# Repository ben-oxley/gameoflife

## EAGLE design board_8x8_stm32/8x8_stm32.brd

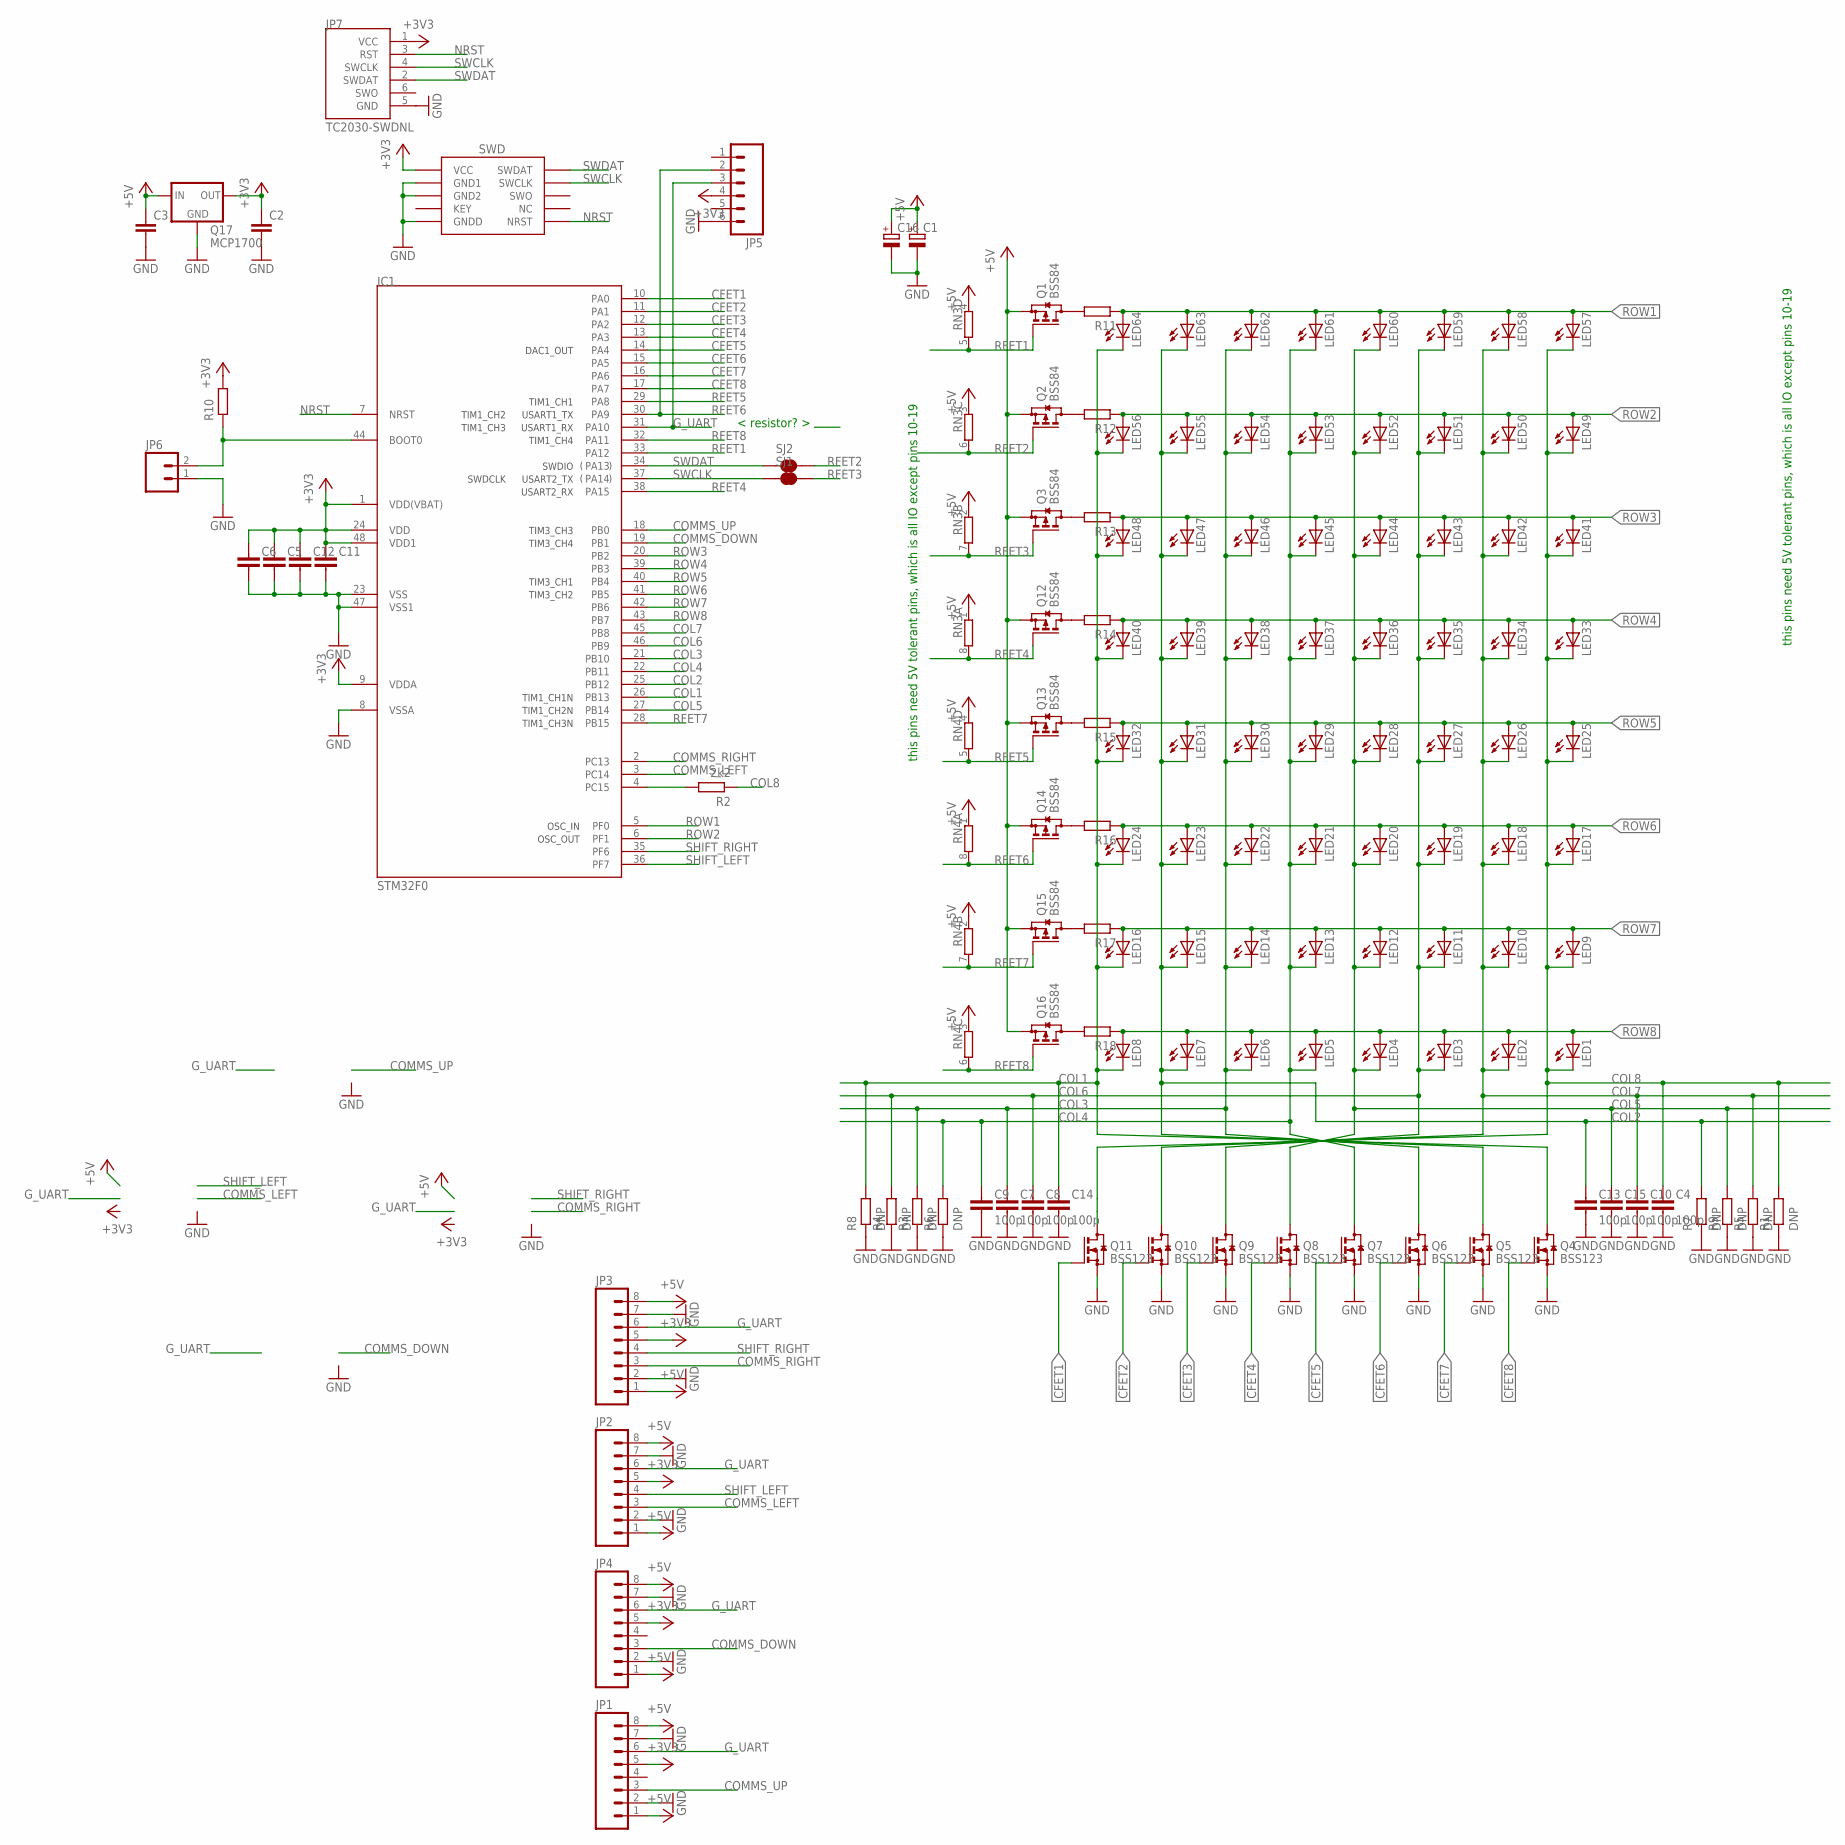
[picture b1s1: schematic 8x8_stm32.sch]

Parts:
C1, C16: CPOL-EUE2-4; E2-4
C2, C3: C-EU050-025X075; C050-025X075
C4, C7, C8, C9, C10, C13, C14, C15: 100p; C0603-N
C5, C6, C11, C12: CAPACITOR0603-N; C0603-N
IC1: STM32F0; TQFP48
J1: SWD_SHROUD; SWD_PTH_SHROUD
JP1, JP2, JP3, JP4: M08; 1X08_ROUND
JP5: M06SILK_FEMALE_PTH; 1X06
JP6: M02PTH; 1X02
JP7: TC2030-SWDNL; TC2030-MCP-NL
LED1, LED2, LED3, LED4, LED5, LED6, LED7, LED8, LED9, LED10, LED11, LED12, LED13, LED14, LED15, LED16, LED17, LED18, LED19, LED20, LED21, LED22, LED23, LED24, LED25, LED26, LED27, LED28, LED29, LED30, LED31, LED32, LED33, LED34, LED35, LED36, LED37, LED38, LED39, LED40, LED41, LED42, LED43, LED44, LED45, LED46, LED47, LED48, LED49, LED50, LED51, LED52, LED53, LED54, LED55, LED56, LED57, LED58, LED59, LED60, LED61, LED62, LED63, LED64: LED5MM/0603; LED5MM/SMD
Q1, Q2, Q3, Q12, Q13, Q14, Q15, Q16: BSS84; SOT23
Q4, Q5, Q6, Q7, Q8, Q9, Q10, Q11: BSS123; SOT23
Q17: MCP1700; TO92-INLINE
R1, R3, R4, R5, R6, R7, R8, R9: DNP; R0603-N
R2: 2k2; R0603-N
R10, R11, R12, R13, R14, R15, R16, R17, R18: RESISTOR0603-N; R0603-N
RN3, RN4: 4R-NEXB38V; EXB38V
SJ1, SJ2: JUMPER-PAD-2-NC_BY_TRACE; PAD-JUMPER-2-NC_BY_TRACE_YES_SILK

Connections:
+3V3: C2.1, C5.1, C6.1, C11.1, C12.1, IC1.1 (VDD(VBAT)), IC1.9 (VDDA), IC1.24 (VDD), IC1.48 (VDD1), J1.1 (VCC), JP1.5, JP2.5, JP3.5, JP4.5, JP5.4, JP7.1 (VCC), Q17.VOUT (OUT), R10.2
+5V: C1.+, C3.1, C16.+, JP1.1, JP1.8, JP2.1, JP2.8, JP3.1, JP3.8, JP4.1, JP4.8, Q1.2 (S), Q2.2 (S), Q3.2 (S), Q12.2 (S), Q13.2 (S), Q14.2 (S), Q15.2 (S), Q16.2 (S), Q17.VIN (IN), RN3.1, RN3.2 (1), RN3.3 (1), RN3.4 (1), RN4.1, RN4.2 (1), RN4.3 (1), RN4.4 (1)
CFET1: IC1.10 (PA0), Q11.1 (G)
CFET2: IC1.11 (PA1), Q10.1 (G)
CFET3: IC1.12 (PA2), Q9.1 (G)
CFET4: IC1.13 (PA3), Q8.1 (G)
CFET5: IC1.14 (PA4), Q7.1 (G)
CFET6: IC1.15 (PA5), Q6.1 (G)
CFET7: IC1.16 (PA6), Q5.1 (G)
CFET8: IC1.17 (PA7), Q4.1 (G)
COL1: C14.1, IC1.26 (PB13), LED8.K (C), LED8.K1 (C), LED16.K (C), LED16.K1 (C), LED24.K (C), LED24.K1 (C), LED32.K (C), LED32.K1 (C), LED40.K (C), LED40.K1 (C), LED48.K (C), LED48.K1 (C), LED56.K (C), LED56.K1 (C), LED64.K (C), LED64.K1 (C), Q4.3 (D), R8.2
COL2: C13.1, IC1.25 (PB12), LED7.K (C), LED7.K1 (C), LED15.K (C), LED15.K1 (C), LED23.K (C), LED23.K1 (C), LED31.K (C), LED31.K1 (C), LED39.K (C), LED39.K1 (C), LED47.K (C), LED47.K1 (C), LED55.K (C), LED55.K1 (C), LED63.K (C), LED63.K1 (C), Q5.3 (D), R7.2
COL3: C7.1, IC1.21 (PB10), LED6.K (C), LED6.K1 (C), LED14.K (C), LED14.K1 (C), LED22.K (C), LED22.K1 (C), LED30.K (C), LED30.K1 (C), LED38.K (C), LED38.K1 (C), LED46.K (C), LED46.K1 (C), LED54.K (C), LED54.K1 (C), LED62.K (C), LED62.K1 (C), Q6.3 (D), R3.2
COL4: C9.1, IC1.22 (PB11), LED5.K (C), LED5.K1 (C), LED13.K (C), LED13.K1 (C), LED21.K (C), LED21.K1 (C), LED29.K (C), LED29.K1 (C), LED37.K (C), LED37.K1 (C), LED45.K (C), LED45.K1 (C), LED53.K (C), LED53.K1 (C), LED61.K (C), LED61.K1 (C), Q7.3 (D), R6.2
COL5: C15.1, IC1.27 (PB14), LED4.K (C), LED4.K1 (C), LED12.K (C), LED12.K1 (C), LED20.K (C), LED20.K1 (C), LED28.K (C), LED28.K1 (C), LED36.K (C), LED36.K1 (C), LED44.K (C), LED44.K1 (C), LED52.K (C), LED52.K1 (C), LED60.K (C), LED60.K1 (C), Q8.3 (D), R9.2
COL6: C8.1, IC1.46 (PB9), LED3.K (C), LED3.K1 (C), LED11.K (C), LED11.K1 (C), LED19.K (C), LED19.K1 (C), LED27.K (C), LED27.K1 (C), LED35.K (C), LED35.K1 (C), LED43.K (C), LED43.K1 (C), LED51.K (C), LED51.K1 (C), LED59.K (C), LED59.K1 (C), Q9.3 (D), R4.2
COL7: C10.1, IC1.45 (PB8), LED2.K (C), LED2.K1 (C), LED10.K (C), LED10.K1 (C), LED18.K (C), LED18.K1 (C), LED26.K (C), LED26.K1 (C), LED34.K (C), LED34.K1 (C), LED42.K (C), LED42.K1 (C), LED50.K (C), LED50.K1 (C), LED58.K (C), LED58.K1 (C), Q10.3 (D), R5.2
COL8: C4.1, LED1.K (C), LED1.K1 (C), LED9.K (C), LED9.K1 (C), LED17.K (C), LED17.K1 (C), LED25.K (C), LED25.K1 (C), LED33.K (C), LED33.K1 (C), LED41.K (C), LED41.K1 (C), LED49.K (C), LED49.K1 (C), LED57.K (C), LED57.K1 (C), Q11.3 (D), R1.2, R2.1
COMMS_DOWN: IC1.19 (PB1), JP4.3
COMMS_LEFT: IC1.3 (PC14), JP2.3
COMMS_RIGHT: IC1.2 (PC13), JP3.3
COMMS_UP: IC1.18 (PB0), JP1.3
GND: C1.-, C2.2, C3.2, C4.2, C5.2, C6.2, C7.2, C8.2, C9.2, C10.2, C11.2, C12.2, C13.2, C14.2, C15.2, C16.-, IC1.8 (VSSA), IC1.23 (VSS), IC1.47 (VSS1), J1.3 (GND1), J1.5 (GND2), J1.9 (GNDD), JP1.2, JP1.7, JP2.2, JP2.7, JP3.2, JP3.7, JP4.2, JP4.7, JP5.6, JP6.1, JP7.5 (GND), Q4.2 (S), Q5.2 (S), Q6.2 (S), Q7.2 (S), Q8.2 (S), Q9.2 (S), Q10.2 (S), Q11.2 (S), Q17.GND, R1.1, R3.1, R4.1, R5.1, R6.1, R7.1, R8.1, R9.1
G_UART: IC1.31 (PA10), JP1.6, JP2.6, JP3.6, JP4.6, JP5.3
unnamed: IC1.44 (BOOT0), JP6.2, R10.1
unnamed: IC1.4 (PC15), R2.2
unnamed: Q1.3 (D), R11.2
unnamed: Q2.3 (D), R12.2
unnamed: Q3.3 (D), R13.2
unnamed: Q12.3 (D), R14.2
unnamed: Q13.3 (D), R15.2
unnamed: Q14.3 (D), R16.2
unnamed: Q15.3 (D), R17.2
unnamed: Q16.3 (D), R18.2
NRST: IC1.7 (NRST), J1.10 (NRST), JP7.3 (RST)
RFET1: IC1.33 (PA12), Q1.1 (G), RN3.5 (2)
RFET2: Q2.1 (G), RN3.6 (2), SJ2.2
RFET3: Q3.1 (G), RN3.7 (2), SJ1.2
RFET4: IC1.38 (PA15), Q12.1 (G), RN3.8 (2)
RFET5: IC1.29 (PA8), Q13.1 (G), RN4.5 (2)
RFET6: IC1.30 (PA9), JP5.2, Q14.1 (G), RN4.8 (2)
RFET7: IC1.28 (PB15), Q15.1 (G), RN4.7 (2)
RFET8: IC1.32 (PA11), Q16.1 (G), RN4.6 (2)
ROW1: IC1.5 (PF0), LED57.A, LED57.A1 (A), LED58.A, LED58.A1 (A), LED59.A, LED59.A1 (A), LED60.A, LED60.A1 (A), LED61.A, LED61.A1 (A), LED62.A, LED62.A1 (A), LED63.A, LED63.A1 (A), LED64.A, LED64.A1 (A), R11.1
ROW2: IC1.6 (PF1), LED49.A, LED49.A1 (A), LED50.A, LED50.A1 (A), LED51.A, LED51.A1 (A), LED52.A, LED52.A1 (A), LED53.A, LED53.A1 (A), LED54.A, LED54.A1 (A), LED55.A, LED55.A1 (A), LED56.A, LED56.A1 (A), R12.1
ROW3: IC1.20 (PB2), LED41.A, LED41.A1 (A), LED42.A, LED42.A1 (A), LED43.A, LED43.A1 (A), LED44.A, LED44.A1 (A), LED45.A, LED45.A1 (A), LED46.A, LED46.A1 (A), LED47.A, LED47.A1 (A), LED48.A, LED48.A1 (A), R13.1
ROW4: IC1.39 (PB3), LED33.A, LED33.A1 (A), LED34.A, LED34.A1 (A), LED35.A, LED35.A1 (A), LED36.A, LED36.A1 (A), LED37.A, LED37.A1 (A), LED38.A, LED38.A1 (A), LED39.A, LED39.A1 (A), LED40.A, LED40.A1 (A), R14.1
ROW5: IC1.40 (PB4), LED25.A, LED25.A1 (A), LED26.A, LED26.A1 (A), LED27.A, LED27.A1 (A), LED28.A, LED28.A1 (A), LED29.A, LED29.A1 (A), LED30.A, LED30.A1 (A), LED31.A, LED31.A1 (A), LED32.A, LED32.A1 (A), R15.1
ROW6: IC1.41 (PB5), LED17.A, LED17.A1 (A), LED18.A, LED18.A1 (A), LED19.A, LED19.A1 (A), LED20.A, LED20.A1 (A), LED21.A, LED21.A1 (A), LED22.A, LED22.A1 (A), LED23.A, LED23.A1 (A), LED24.A, LED24.A1 (A), R16.1
ROW7: IC1.42 (PB6), LED9.A, LED9.A1 (A), LED10.A, LED10.A1 (A), LED11.A, LED11.A1 (A), LED12.A, LED12.A1 (A), LED13.A, LED13.A1 (A), LED14.A, LED14.A1 (A), LED15.A, LED15.A1 (A), LED16.A, LED16.A1 (A), R17.1
ROW8: IC1.43 (PB7), LED1.A, LED1.A1 (A), LED2.A, LED2.A1 (A), LED3.A, LED3.A1 (A), LED4.A, LED4.A1 (A), LED5.A, LED5.A1 (A), LED6.A, LED6.A1 (A), LED7.A, LED7.A1 (A), LED8.A, LED8.A1 (A), R18.1
SHIFT_LEFT: IC1.36 (PF7), JP2.4
SHIFT_RIGHT: IC1.35 (PF6), JP3.4
SWCLK: IC1.37 (PA14), J1.4 (SWCLK), JP7.4 (SWCLK), SJ1.1
SWDAT: IC1.34 (PA13), J1.2 (SWDAT), JP7.2 (SWDAT), SJ2.1

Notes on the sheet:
this pins need 5V tolerant pins, which is all IO except pins 10-19
< resistor? >

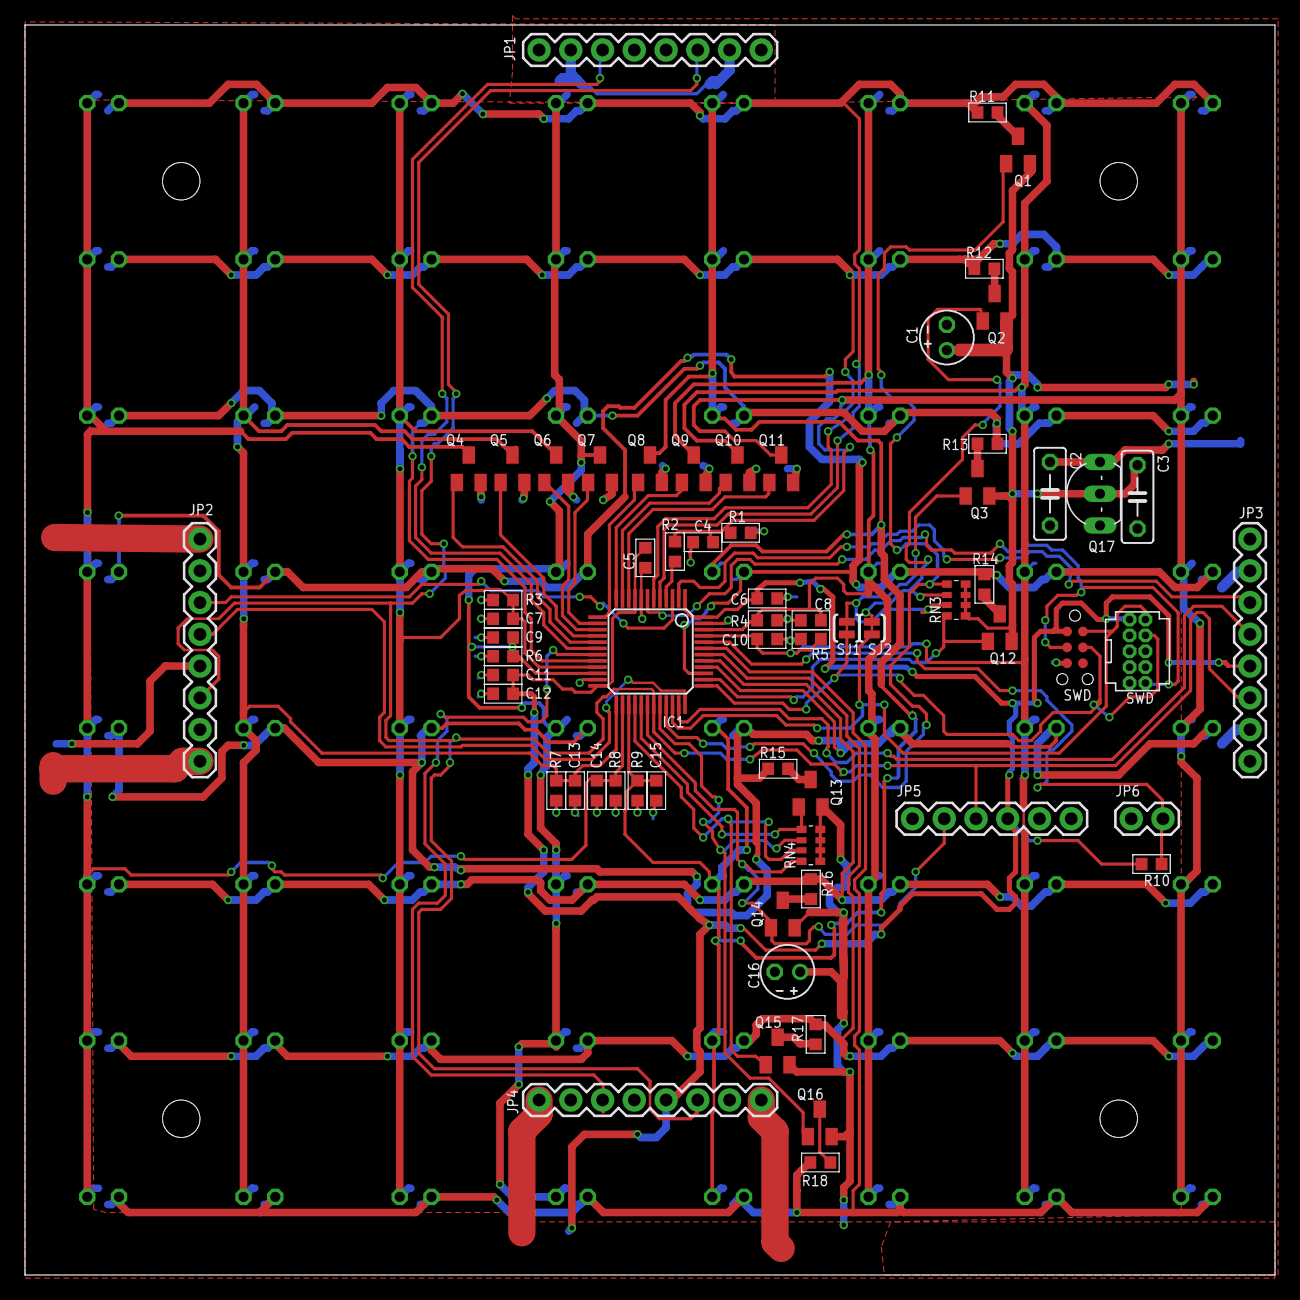
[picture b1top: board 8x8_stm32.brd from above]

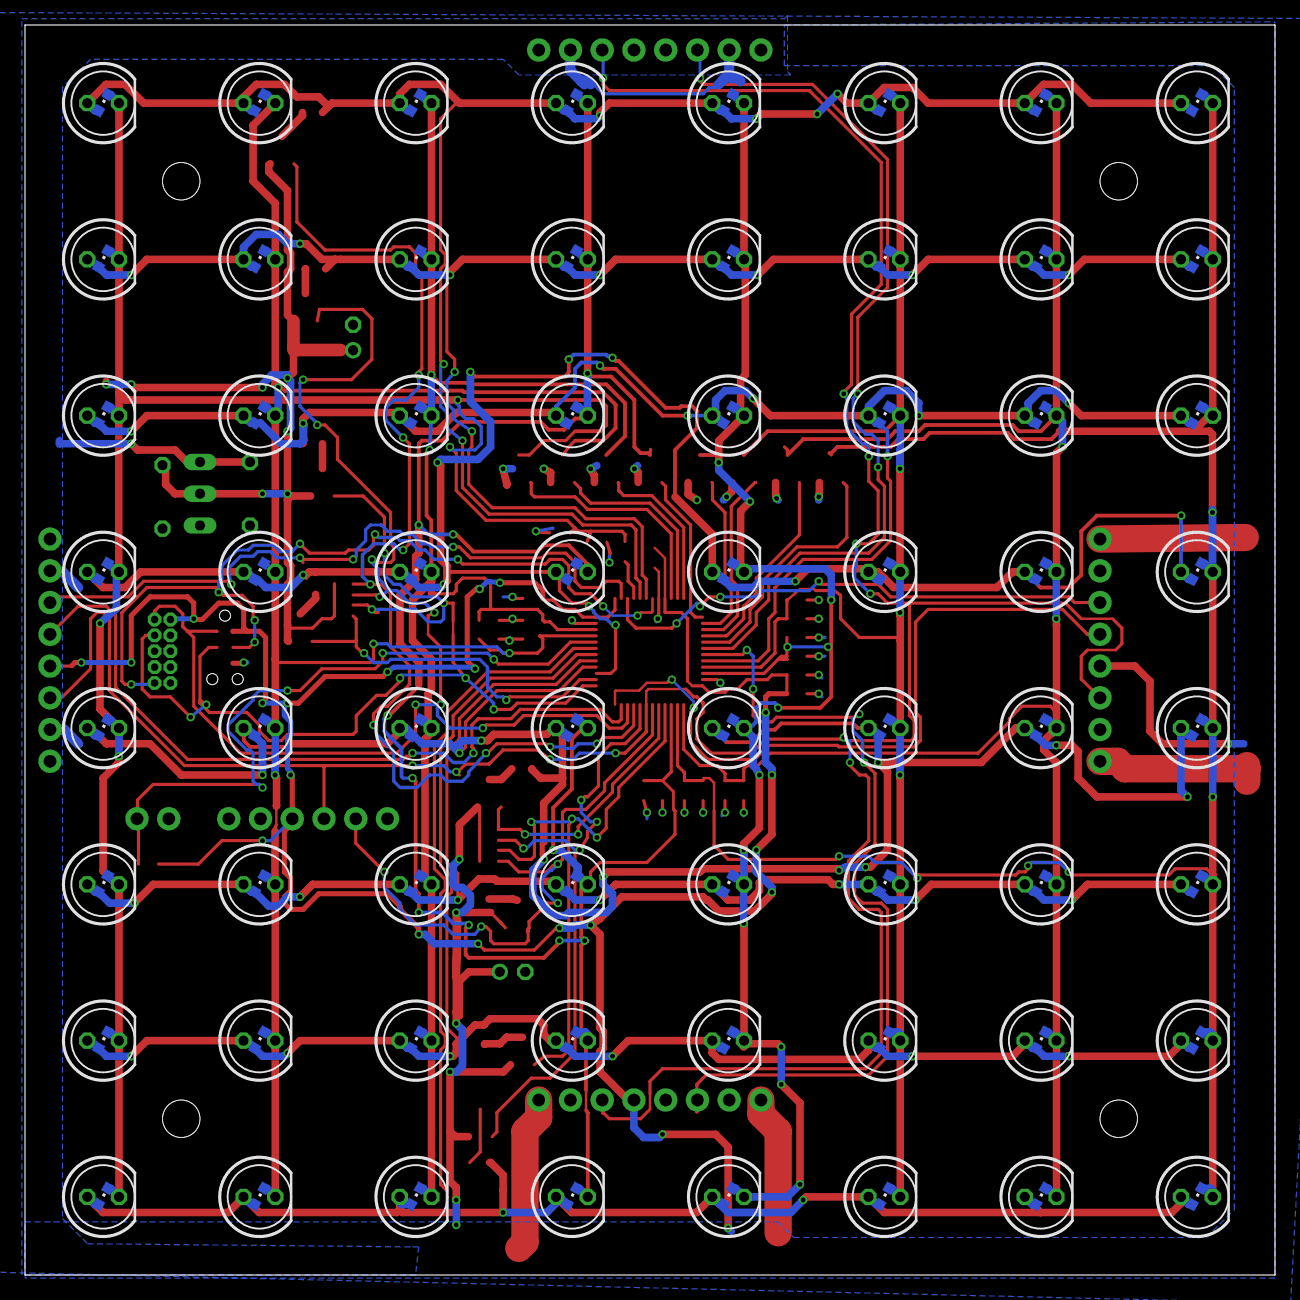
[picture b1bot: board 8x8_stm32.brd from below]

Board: 2 copper layers, 100.0 x 100.0 mm, 128 parts (64 on the bottom side), 55 nets.

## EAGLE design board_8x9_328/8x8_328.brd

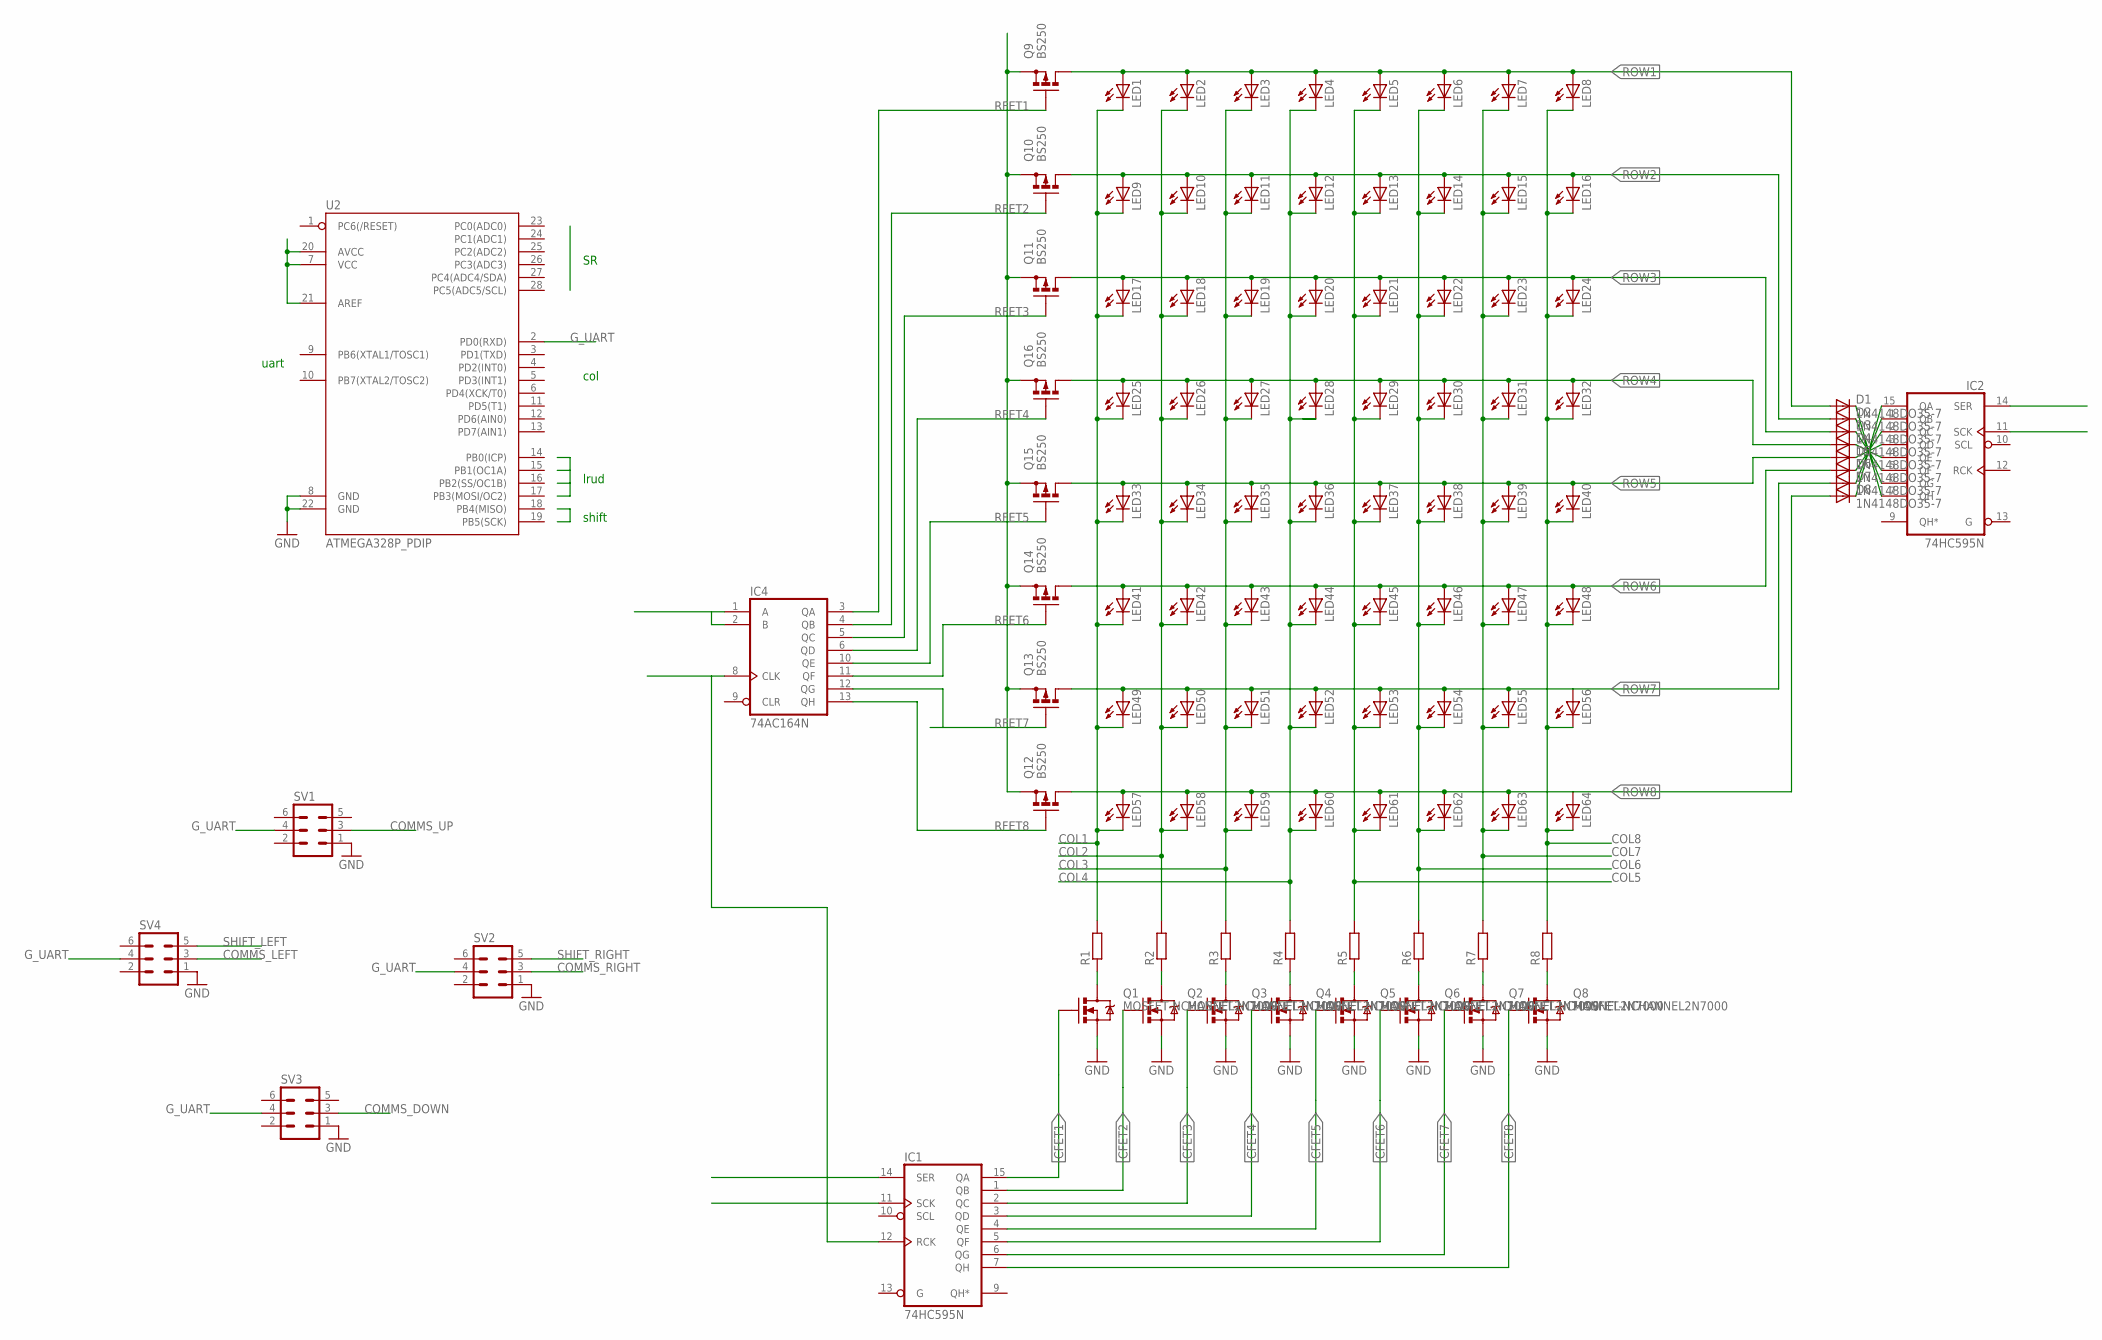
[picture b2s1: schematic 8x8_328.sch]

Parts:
D1, D2, D3, D4, D5, D6, D7, D8: 1N4148DO35-7; DO35-7
IC1, IC2: 74HC595N; DIL16
IC4: 74AC164N; DIL14
LED1, LED2, LED3, LED4, LED5, LED6, LED7, LED8, LED9, LED10, LED11, LED12, LED13, LED14, LED15, LED16, LED17, LED18, LED19, LED20, LED21, LED22, LED23, LED24, LED25, LED26, LED27, LED28, LED29, LED30, LED31, LED32, LED33, LED34, LED35, LED36, LED37, LED38, LED39, LED40, LED41, LED42, LED43, LED44, LED45, LED46, LED47, LED48, LED49, LED50, LED51, LED52, LED53, LED54, LED55, LED56, LED57, LED58, LED59, LED60, LED61, LED62, LED63, LED64: LED5MM
Q1, Q2, Q3, Q4, Q5, Q6, Q7, Q8: MOSFET-NCHANNEL2N7000; TO-92
Q9, Q10, Q11, Q12, Q13, Q14, Q15, Q16: BS250; SOT54E
R1, R2, R3, R4, R5, R6, R7, R8: R-EU_0207/10; 0207/10
SV1, SV2, SV3, SV4: MA03-2
U2: ATMEGA328P_PDIP; DIL28-3

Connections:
CFET1: IC1.15 (QA), Q1.2 (G)
CFET2: IC1.1 (QB), Q2.2 (G)
CFET3: IC1.2 (QC), Q3.2 (G)
CFET4: IC1.3 (QD), Q4.2 (G)
CFET5: IC1.4 (QE), Q5.2 (G)
CFET6: IC1.5 (QF), Q6.2 (G)
CFET7: IC1.6 (QG), Q7.2 (G)
CFET8: IC1.7 (QH), Q8.2 (G)
COL1: LED1.K (C), LED9.K (C), LED17.K (C), LED25.K (C), LED33.K (C), LED41.K (C), LED49.K (C), LED57.K (C), R1.2
COL2: LED2.K (C), LED10.K (C), LED18.K (C), LED26.K (C), LED34.K (C), LED42.K (C), LED50.K (C), LED58.K (C), R2.2
COL3: LED3.K (C), LED11.K (C), LED19.K (C), LED27.K (C), LED35.K (C), LED43.K (C), LED51.K (C), LED59.K (C), R3.2
COL4: LED4.K (C), LED12.K (C), LED20.K (C), LED28.K (C), LED36.K (C), LED44.K (C), LED52.K (C), LED60.K (C), R4.2
COL5: LED5.K (C), LED13.K (C), LED21.K (C), LED29.K (C), LED37.K (C), LED45.K (C), LED53.K (C), LED61.K (C), R5.2
COL6: LED6.K (C), LED14.K (C), LED22.K (C), LED30.K (C), LED38.K (C), LED46.K (C), LED54.K (C), LED62.K (C), R6.2
COL7: LED7.K (C), LED15.K (C), LED23.K (C), LED31.K (C), LED39.K (C), LED47.K (C), LED55.K (C), LED63.K (C), R7.2
COL8: LED8.K (C), LED16.K (C), LED24.K (C), LED32.K (C), LED40.K (C), LED48.K (C), LED56.K (C), LED64.K (C), R8.2
COMMS_DOWN: SV3.3
COMMS_LEFT: SV4.3
COMMS_RIGHT: SV2.3
COMMS_UP: SV1.3
GND: IC1.8 (GND), IC2.8 (GND), IC4.7 (GND), Q1.1 (S), Q2.1 (S), Q3.1 (S), Q4.1 (S), Q5.1 (S), Q6.1 (S), Q7.1 (S), Q8.1 (S), SV1.1, SV2.1, SV3.1, SV4.1, U2.8 (GND), U2.22 (GND)
G_UART: SV1.4, SV2.4, SV3.4, SV4.4, U2.2 (PD0(RXD))
unnamed: Q8.3 (D), R8.1
unnamed: Q7.3 (D), R7.1
unnamed: Q6.3 (D), R6.1
unnamed: Q5.3 (D), R5.1
unnamed: Q4.3 (D), R4.1
unnamed: Q3.3 (D), R3.1
unnamed: Q2.3 (D), R2.1
unnamed: Q1.3 (D), R1.1
unnamed: IC1.12 (RCK), IC4.8 (CLK)
unnamed: IC4.1 (A), IC4.2 (B)
unnamed: D1.C, IC2.7 (QH)
unnamed: U2.7 (VCC), U2.20 (AVCC), U2.21 (AREF)
unnamed: D8.C, IC2.15 (QA)
unnamed: D7.C, IC2.1 (QB)
unnamed: D6.C, IC2.2 (QC)
unnamed: D5.C, IC2.3 (QD)
unnamed: D4.C, IC2.4 (QE)
unnamed: D3.C, IC2.5 (QF)
unnamed: D2.C, IC2.6 (QG)
unnamed: Q9.S, Q10.S, Q11.S, Q12.S, Q13.S, Q14.S, Q15.S, Q16.S
RFET1: IC4.3 (QA), Q9.G
RFET2: IC4.4 (QB), Q10.G
RFET3: IC4.5 (QC), Q11.G
RFET4: IC4.6 (QD), Q16.G
RFET5: IC4.10 (QE), Q15.G
RFET6: IC4.11 (QF), Q14.G
RFET7: IC4.12 (QG), Q13.G
RFET8: IC4.13 (QH), Q12.G
ROW1: D1.A, LED1.A, LED2.A, LED3.A, LED4.A, LED5.A, LED6.A, LED7.A, LED8.A, Q9.D
ROW2: D2.A, LED9.A, LED10.A, LED11.A, LED12.A, LED13.A, LED14.A, LED15.A, LED16.A, Q10.D
ROW3: D3.A, LED17.A, LED18.A, LED19.A, LED20.A, LED21.A, LED22.A, LED23.A, LED24.A, Q11.D
ROW4: D4.A, LED25.A, LED26.A, LED27.A, LED28.A, LED29.A, LED30.A, LED31.A, LED32.A, Q16.D
ROW5: D5.A, LED33.A, LED34.A, LED35.A, LED36.A, LED37.A, LED38.A, LED39.A, LED40.A, Q15.D
ROW6: D6.A, LED41.A, LED42.A, LED43.A, LED44.A, LED45.A, LED46.A, LED47.A, LED48.A, Q14.D
ROW7: D7.A, LED49.A, LED50.A, LED51.A, LED52.A, LED53.A, LED54.A, LED55.A, LED56.A, Q13.D
ROW8: D8.A, LED57.A, LED58.A, LED59.A, LED60.A, LED61.A, LED62.A, LED63.A, LED64.A, Q12.D
SHIFT_LEFT: SV4.5
SHIFT_RIGHT: SV2.5
VCC: IC1.16 (VCC), IC2.16 (VCC), IC4.14 (VCC)

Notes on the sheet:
col
lrud
shift
uart

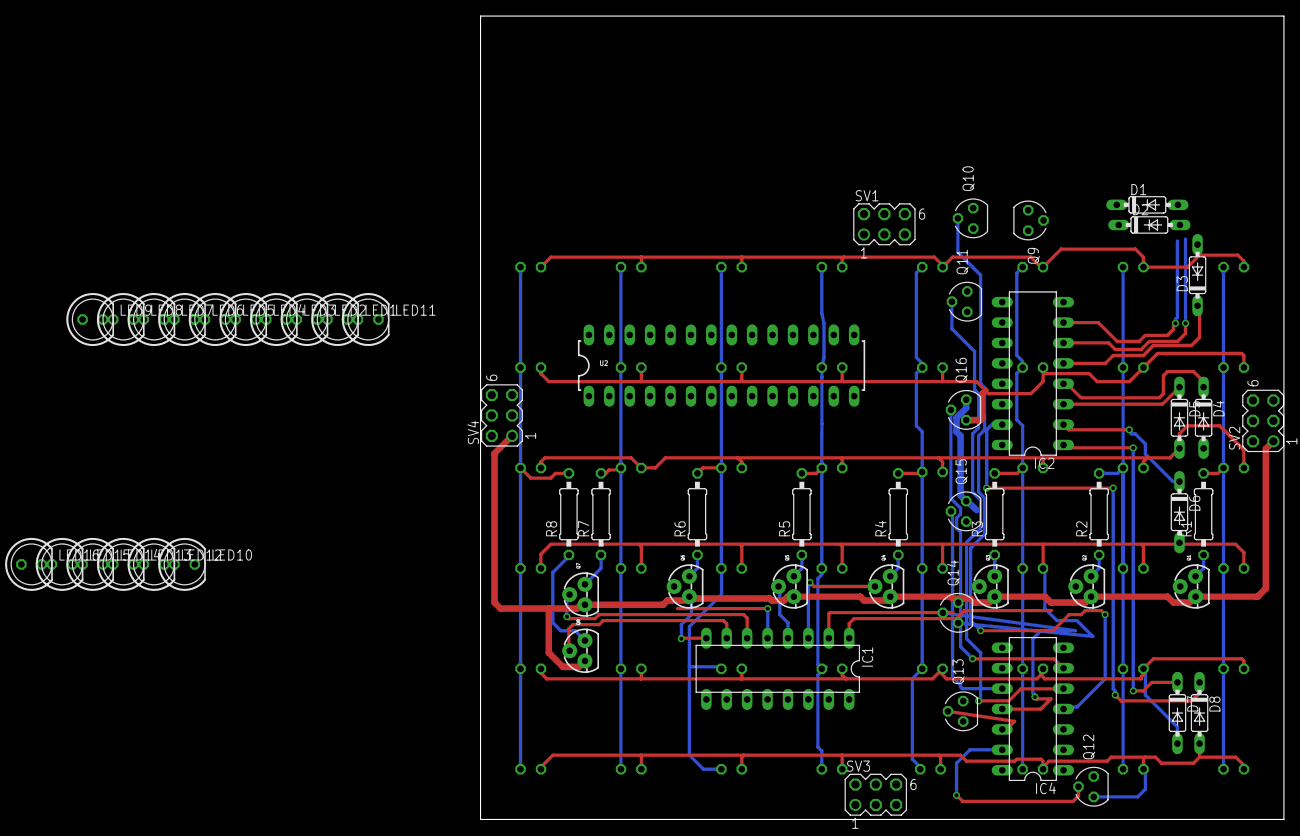
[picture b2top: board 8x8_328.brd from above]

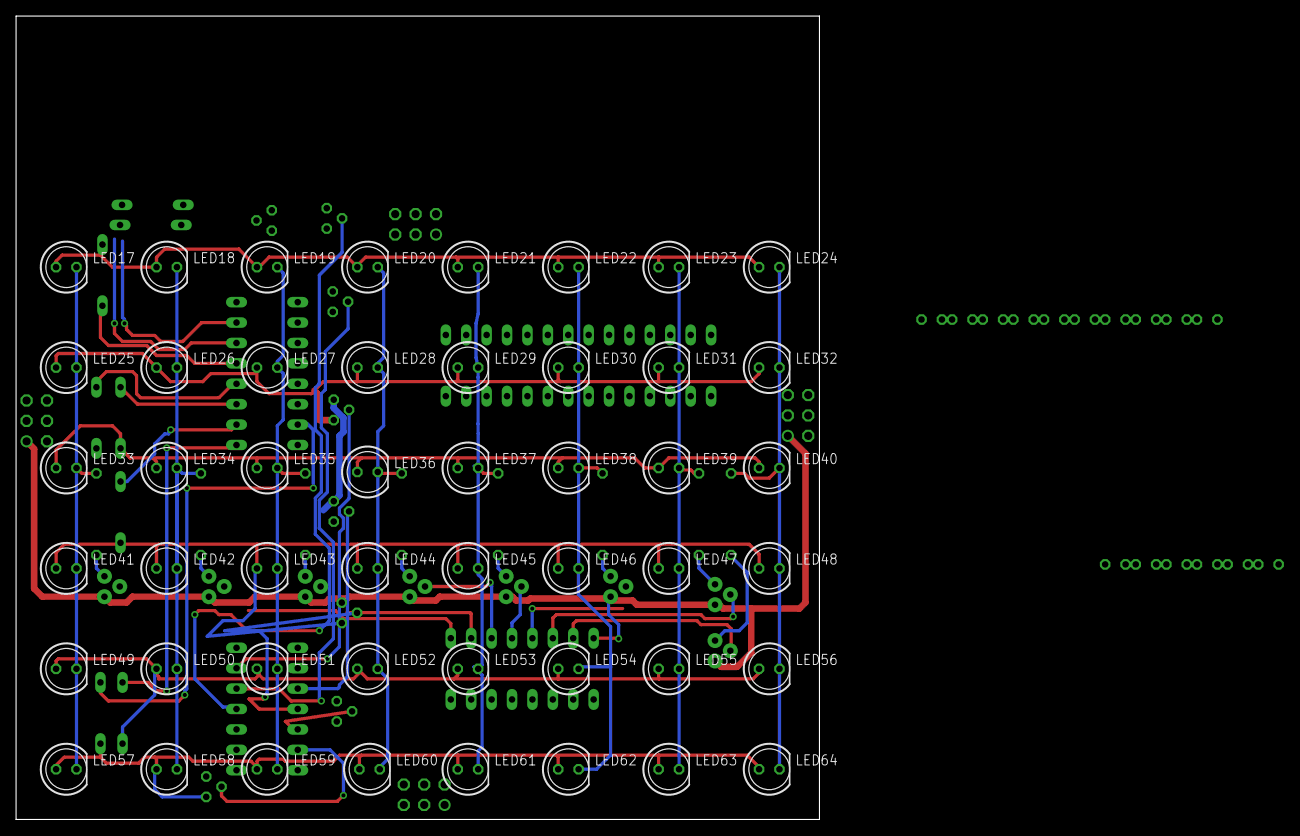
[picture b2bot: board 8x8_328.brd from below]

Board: 2 copper layers, 100.0 x 100.0 mm, 104 parts (48 on the bottom side), 55 nets.

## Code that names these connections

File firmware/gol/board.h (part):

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/*
 *  GPIOA setup:
 *
 * PA0  - COL_FET_1                    (output, pushpull).
 * PA1  - COL_FET_2                    (output, pushpull).
 * PA2  - COL_FET_3                    (output, pushpull).
 * PA3  - COL_FET_4                    (output, pushpull).
 * PA4  - COL_FET_5                    (output, pushpull).
 * PA5  - COL_FET_6                    (output, pushpull).
 * PA6  - COL_FET_7                    (output, pushpull).
 * PA7  - COL_FET_8                    (output, pushpull).
 * PA8  - ROW_FET_5                    (output, pushpull).
 * PA9  - ROW_FET_6                    (output, pushpull).
 * PA10 - G_UART                       (input, floating).
 * PA11 - ROW_FET_8                    (output, pushpull).
 * PA12 - ROW_FET_1                    (output, pushpull).
 * PA13 - ROW_FET_2                    (output, pushpull).
 * PA14 - ROW_FET_3                    (output, pushpull).
 * PA15 - ROW_FET_4                    (output, pushpull).
*/
#define VAL_GPIOA_MODER                (PIN_MODE_OUTPUT(GPIOA_COL_FET_1) | \
                                        PIN_MODE_OUTPUT(GPIOA_COL_FET_2) | \
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/*
 *  GPIOB setup:
 *
 * PB0  - COMMS_UP                     (input, floating).
 * PB1  - COMMS_DOWN                   (input, floating).
 * PB2  - ROW3                         (input, floating).
 * PB3  - ROW4                         (input, floating).
 * PB4  - ROW5                         (input, floating).
 * PB5  - ROW6                         (input, floating).
 * PB6  - ROW7                         (input, floating).
 * PB7  - ROW8                         (input, floating).
 * PB8  - COL7                         (input, floating).
 * PB9  - COL6                         (input, floating).
 * PB10 - COL3                         (input, floating).
 * PB11 - COL4                         (input, floating).
 * PB12 - COL2                         (input, floating).
 * PB13 - COL1                         (input, floating).
 * PB14 - COL5                         (input, floating).
 * PB15 - ROW_FET_7                    (output, pushpull).
*/
#define VAL_GPIOB_MODER                (PIN_MODE_INPUT(GPIOB_COMMS_UP) | \
                                        PIN_MODE_INPUT(GPIOB_COMMS_DOWN) | \
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 * PC10 - PIN10                        (unused).
 * PC11 - PIN11                        (unused).
 * PC12 - PIN12                        (unused).
 * PC13 - COMMS_RIGHT                  (input, floating).
 * PC14 - COMMS_LEFT                   (input, floating).
 * PC15 - COL8                         (input, floating).
*/
#define VAL_GPIOC_MODER                (PIN_MODE_INPUT(GPIOC_PIN0) | \
                                        PIN_MODE_INPUT(GPIOC_PIN1) | \
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/*
 *  GPIOD setup:
 *
 * PD0  - PIN0                         (unused).
 * PD1  - PIN1                         (unused).
 * PD2  - PIN2                         (unused).
 * PD3  - PIN3                         (unused).
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/*
 *  GPIOF setup:
 *
 * PF0  - ROW1                         (input, floating).
 * PF1  - ROW2                         (input, floating).
 * PF2  - PIN2                         (unused).
 * PF3  - PIN3                         (unused).
 * PF4  - PIN4                         (unused).
 * PF5  - PIN5                         (unused).
 * PF6  - SHIFT_LEFT                   (input, floating).
 * PF7  - SHIFT_RIGHT                  (input, floating).
 * PF8  - PIN8                         (unused).
 * PF9  - PIN9                         (unused).
 * PF10 - PIN10                        (unused).
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
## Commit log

2015-12-16 started 8x8 stm32 board
2015-12-17 adding led photodide sim
2015-12-20 playing about with different deisgns
2015-12-21 rename
2015-12-21 postioning components to the top edge
2015-12-22 adding a couple of notes
2015-12-23 adding test projet
2015-12-28 'done' schematic
2015-12-28 chnaging to combined led footprint
2015-12-29 routing...
2016-01-01 more routig..
2016-01-03 almost done
2016-01-04 some prodding
2016-01-18 first prototype almost done
2016-01-25 changed something...
2016-03-09 Updated boards based on etc
2016-03-09 Added CAM files for DirtyPCBs
2016-07-23 Eclipse project set for ChibiOS
2016-07-23 Updated eagle parts
2016-07-23 Created LED jig for soldering
2016-07-23 Uploaded farnell shopping cart
2016-07-24 Update code to try and fix programming issues

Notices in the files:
firmware/gol/board.h:
ChibiOS - Copyright (C) 2006..2016 Giovanni Di Sirio
Licensed under the Apache License, Version 2.0 (the "License");
parts and their libraries:
SparkFun-Connectors: Licensing: Creative Commons ShareAlike 4.0 International - https://creativecommons.org/licenses/by-sa/4.0
tag-connect: ©2009 ROFA.cz - modified and updated by Robert Darlington ‹rdarlington@gmail.com›
